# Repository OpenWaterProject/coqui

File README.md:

coqui
=====

For the latest information & tutorials about the Coqui, please visit the [Coqui Wiki on Public Lab](http://publiclab.org/wiki/coqui).

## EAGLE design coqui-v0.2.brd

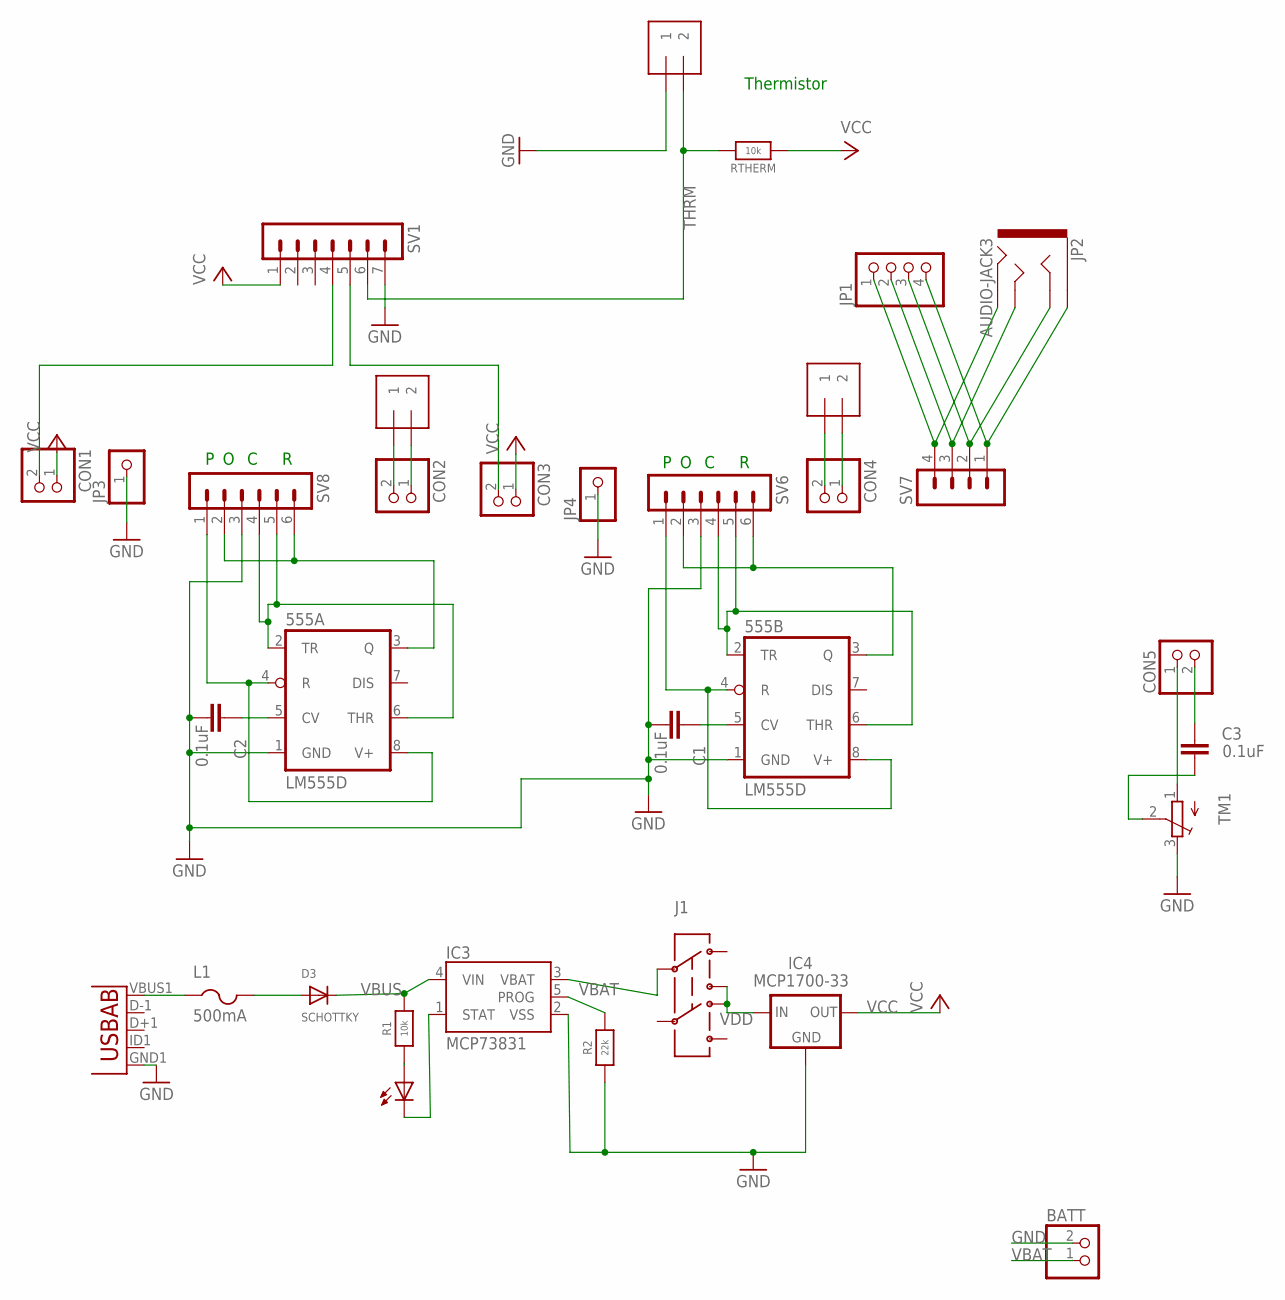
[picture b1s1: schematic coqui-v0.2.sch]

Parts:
555A, 555B: LM555D; SO08
BATT: JST_2PIN-SMT-RA; JST-PH-2-SMT-RA
C1, C2, C3: 0.1uF; 0603-CAP
CHG: 0805; CHIPLED_0805
CON1, CON2, CON3, CON4, CON5: PINHD-1X2; 1X02
D3: SCHOTTKY; SOD-123FL
IC3: MCP73831; SOT23-5
IC4: MCP1700-33; SOT89
IN1, IN2: 1X2-3.5MM
J1: AYZ0202
JP1: PINHD-1X4/90; 1X04/90
JP2: AUDIO-JACK3; AUDIO-JACK-TRRS-SMD
JP3, JP4: PINHD-1X1; 1X01
L1: 500mA; R1206
R1: 10k; 0603-NO
R2: 22k; 0603-NO
RTHERM: 10k; 0603-NO
SV1: MA07-1
SV6, SV8: MA06-1
SV7: MA04-1
THRM: 1X2-3.5MM
TM1: TRIMPOTTC33X; TC33X
U$4: USB-AB""; USB-AB-MICRO-SMD_V02_BOSS

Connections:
AOUT: 555A.3 (Q), SV8.2, SV8.6
AOUT1: 555B.3 (Q), SV6.2, SV6.6
GND: 555A.1 (GND), 555B.1 (GND), BATT.2 (1), C1.1, C2.1, IC3.2 (VSS), IC4.1 (GND), JP3.1, JP4.1, R2.1, SV1.7, SV6.3, SV8.3, THRM.1, TM1.3 (E), U$4.GND1 (GND)
unnamed: 555B.2 (TR), 555B.6 (THR), SV6.4, SV6.5
unnamed: 555B.5 (CV), C1.2
unnamed: IC3.5 (PROG), R2.2
unnamed: CHG.A, R1.1
unnamed: CHG.C, IC3.1 (STAT)
unnamed: JP1.4, JP2.EARTH, SV7.1
unnamed: JP1.3, JP2.RING1, SV7.2
unnamed: JP1.2, JP2.TIP, SV7.3
unnamed: JP1.1, JP2.RING2, SV7.4
unnamed: CON2.2, IN1.1
unnamed: 555A.2 (TR), 555A.6 (THR), SV8.4, SV8.5
unnamed: L1.1, U$4.VBUS1 (VBUS)
unnamed: D3.A, L1.2
unnamed: 555A.5 (CV), C2.2
unnamed: CON2.1, IN1.2
unnamed: CON4.2, IN2.1
unnamed: CON4.1, IN2.2
unnamed: CON1.2, SV1.4
unnamed: CON3.2, SV1.5
unnamed: CON5.1, TM1.1 (A)
unnamed: C3.2, CON5.2
unnamed: C3.1, TM1.2 (S)
THRM: RTHERM.2, SV1.6, THRM.2
VAIN: 555A.4 (R), 555A.8 (V+), SV8.1
VAIN1: 555B.4 (R), 555B.8 (V+), SV6.1
VBAT: BATT.1 (2), IC3.3 (VBAT), J1.2
VBUS: D3.C, IC3.4 (VIN), R1.2
VCC: CON1.1, CON3.1, IC4.3 (OUT), RTHERM.1, SV1.1
VDD: IC4.2 (IN), J1.1 (3), J1.6 (4)

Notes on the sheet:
Thermistor

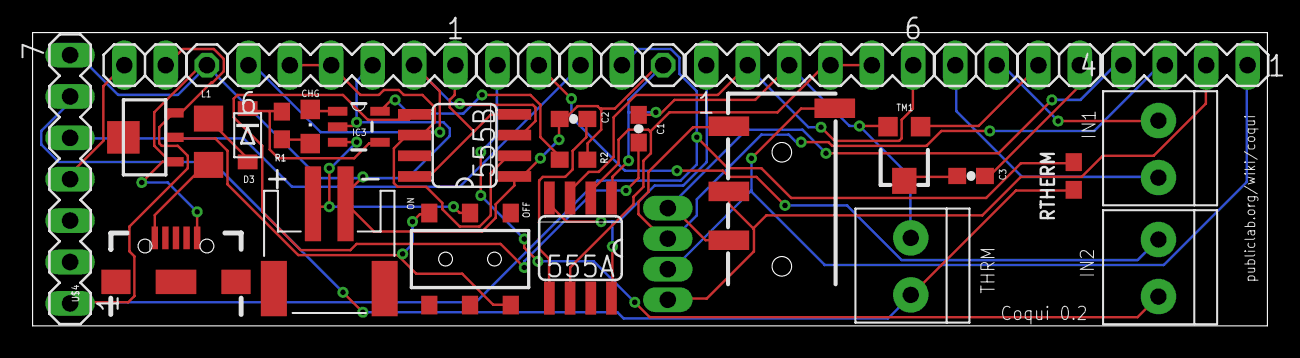
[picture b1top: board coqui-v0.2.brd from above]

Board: 2 copper layers, 75.8 x 18.0 mm, 33 parts (0 on the bottom side), 32 nets.

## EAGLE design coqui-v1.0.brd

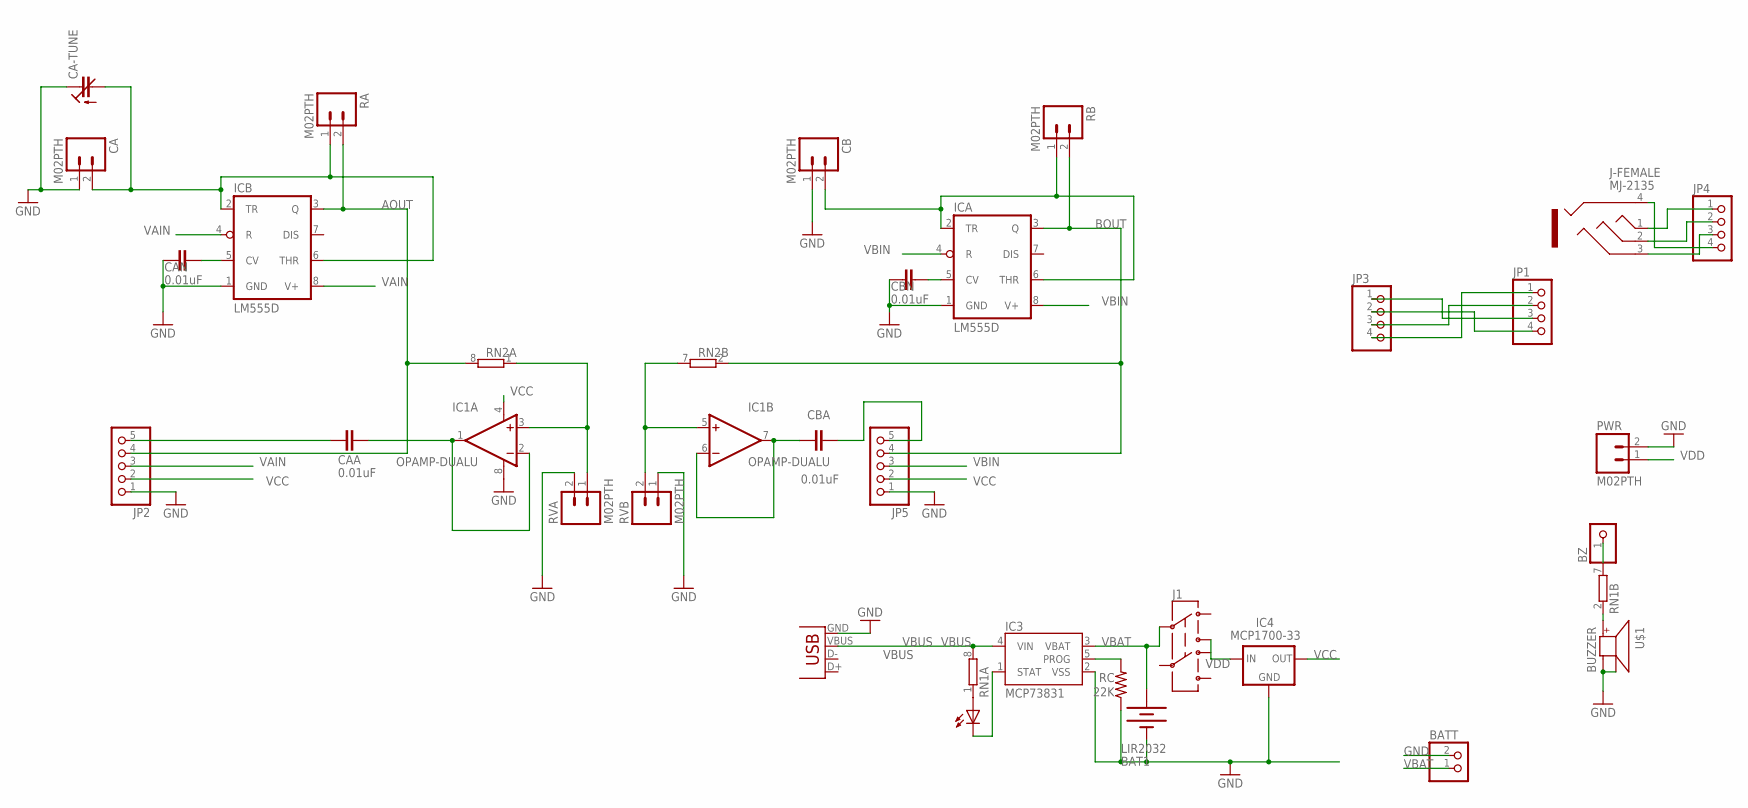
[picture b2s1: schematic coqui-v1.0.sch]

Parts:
BAT1: LIR2032; BATTCOM_20MM_PTH_SMT
BATT: JST_2PIN-SMT-RA; JST-PH-2-SMT-RA
BZ: PINHD-1X1; 1X01
CA: M02PTH; 1X02
CA-TUNE: C-TRIMMTZBX4; CTRIMTZBX4
CAA: 0.01uF; C0805@1
CAN: 0.01uF; C0805@1
CB: M02PTH; 1X02
CBA: 0.01uF; C0805@1
CBN: 0.01uF; C0805@1
CHG: 0805; CHIPLED_0805
IC1: OPAMP-DUALU; SO08
IC3: MCP73831; SOT23-5
IC4: MCP1700-33; SOT89
ICA: LM555D; SO08
ICB: LM555D; SO08
J1: AYZ0202
J-FEMALE: MJ-2135
JP1: PINHD-1X4/90; 1X04/90
JP2, JP5: PINHD-1X5; 1X05
JP3, JP4: PINHD-1X4; 1X04
PWR: M02PTH; 1X02
RA: M02PTH; 1X02
RB: M02PTH; 1X02
RC: 22K; R0805
RN1, RN2: 4R-NEXB38V; EXB38V
RVA: M02PTH; 1X02
RVB: M02PTH; 1X02
U$1: BUZZER; SMT-8585-BUZZER
X1: USBSMD; USB-MINIB

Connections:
AOUT: ICB.3 (Q), JP2.4, RA.2, RN2.8 (2)
BOUT: ICA.3 (Q), JP5.4, RB.2, RN2.2 (1)
GND: BAT1.P$1 (-), BATT.2 (1), CA.1, CA-TUNE.1 (E), CAN.1, CB.1, CBN.1, IC1.8 (V+), IC3.2 (VSS), IC4.1 (GND), ICA.1 (GND), ICB.1 (GND), JP2.1, JP5.1, PWR.2, RC.1, RVA.2, RVB.1, U$1.-, U$1.A-, X1.GND
unnamed: J-FEMALE.1, JP4.1
unnamed: J-FEMALE.2, JP4.2
unnamed: IC3.5 (PROG), RC.2
unnamed: J-FEMALE.3, JP4.3
unnamed: CHG.C, IC3.1 (STAT)
unnamed: J-FEMALE.4, JP4.4
unnamed: BZ.1, RN1.7 (2)
unnamed: CHG.A, RN1.1
unnamed: CAA.1, JP2.5
unnamed: CAA.2, IC1.1 (OUT), IC1.2 (-IN)
unnamed: CA.2, CA-TUNE.2 (A), ICB.2 (TR), ICB.6 (THR), RA.1
unnamed: RN1.2 (1), U$1.+
unnamed: CBA.2, JP5.5
unnamed: CAN.2, ICB.5 (CV)
unnamed: CBN.2, ICA.5 (CV)
unnamed: CB.2, ICA.2 (TR), ICA.6 (THR), RB.1
unnamed: JP1.1, JP3.4
unnamed: JP1.3, JP3.1
unnamed: JP1.2, JP3.3
unnamed: JP1.4, JP3.2
unnamed: IC1.3 (+IN), IC1.5 (+IN), RN2.1, RN2.7 (2), RVA.1, RVB.2
unnamed: CBA.1, IC1.6 (-IN), IC1.7 (OUT)
VAIN: ICB.4 (R), ICB.8 (V+), JP2.3
VBAT: BAT1.P$2 (+), BATT.1 (2), IC3.3 (VBAT), J1.2
VBIN: ICA.4 (R), ICA.8 (V+), JP5.3
VBUS: IC3.4 (VIN), RN1.8 (2), X1.VBUS
VCC: IC1.4 (V-), IC4.3 (OUT), JP2.2, JP5.2
VDD: IC4.2 (IN), J1.1 (3), PWR.1

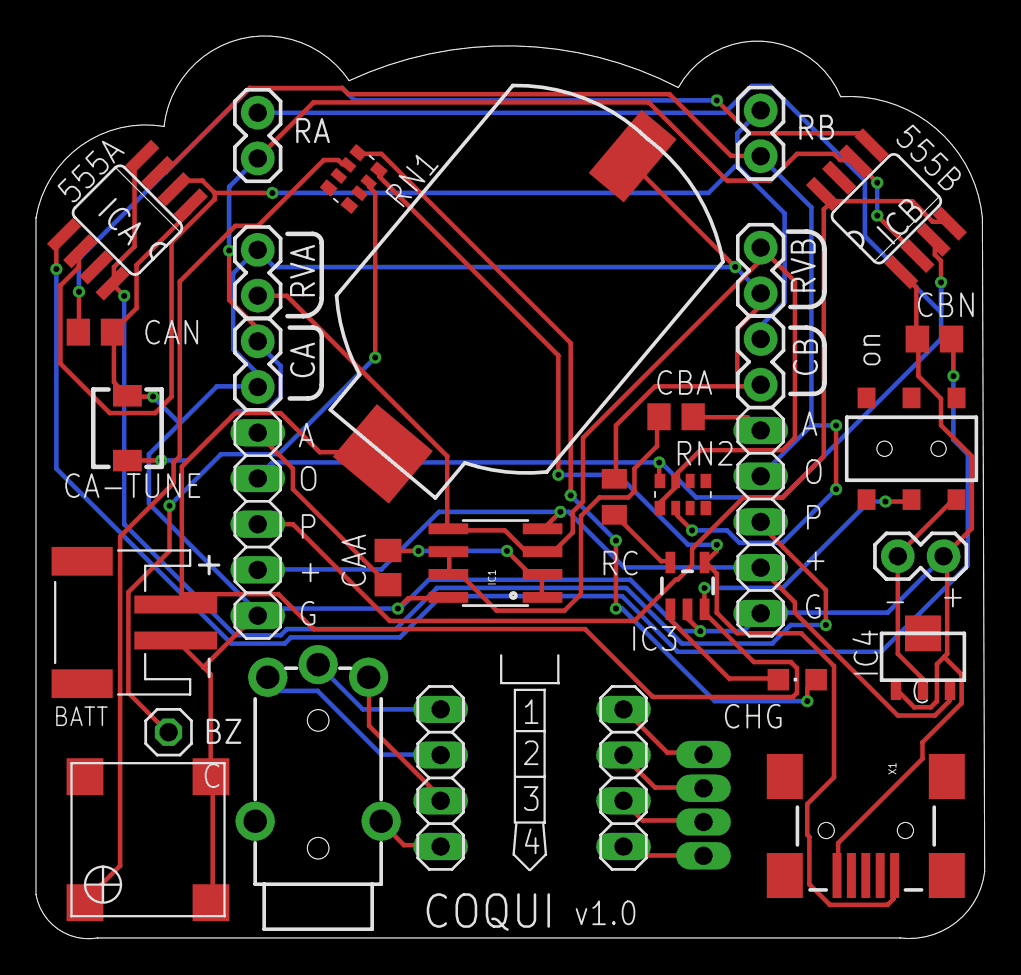
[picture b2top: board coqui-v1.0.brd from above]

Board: 2 copper layers, 52.7 x 50.2 mm, 33 parts (0 on the bottom side), 31 nets.

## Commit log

2015-02-05 Create gh-pages branch via GitHub

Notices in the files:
parts and their libraries:
SparkFun-Connectors: Licensing: Creative Commons ShareAlike 4.0 International - https://creativecommons.org/licenses/by-sa/4.0
microbuilder: This work is placed in the public domain, and may be freely used for commercial and non-commercial work with the following conditions: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
